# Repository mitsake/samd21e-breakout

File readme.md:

# Small SAMD21 breakout

This is a small, simple breakout for the Microchip (formerly Atmel) [ATSAMD21E][] series of chips in the TQFP package. I designed it mostly for something to do while locked down at home, but also so that I could use the bare ICs I had spare from previous projects.

[ATSAMD21E]: https://www.microchip.com/wwwproducts/en/ATSAMD21E18

Most I/O pins are broken out, with the exception of PA00/01 (XIN32 and XOUT32 for the watch crystal) and PA24/25 (D- and D+ for USB). The SWD interface is available via either the header, or through the [SOICbite][] connector opposite the USB footprint. There's an onboard regulator, crystal, reset button, and USB jack make things a bit more convenient. 

This design is based on Adafruit's [Trinket M0][] as well as Technoblogy's Minimal [ATSAMD21 Computer][minimalcomp].

[SOICbite]: https://github.com/SimonMerrett/SOICbite/
[Trinket M0]: https://www.adafruit.com/product/3500
[minimalcomp]: http://www.technoblogy.com/show?2833

## BoM

| Reference | Quantity | Value                      | Footprint                   |
| --------- | -------- | -------------------------- | --------------------------- |
| C1, C2    | 2        | 10 μF, > 6 V               | 0603                        |
| C3, C4    | 2        | 1 μF, > 4 V                | 0603                        |
| C5        | 1        | 0.1 μF, > 4 V              | 0603                        |
| C6, C7    | 2        | 10 pF, > 4 V               | 0603                        |
| J1        | 1        | Micro-USB jack             | [Molex 105017-0001][1]      |
| SW1       | 1        | Push switch                | [Alps SKRKAEE020][2]        |
| U1        | 1        | AP2112K-3.3                | SOT23-5                     |
| U2        | 1        | ATSAMD21Exx                | TQFP-32                     |
| Y1        | 1        | 32.768 kHz, < 12.5 pF load | [Micro Crystal CM7V-T1A][3] |

[1]: https://www.molex.com/molex/products/part-detail/io_connectors/1050170001
[2]: https://tech.alpsalpine.com/prod/e/html/tact/surfacemount/skrk/skrk_list.html
[3]: https://www.microcrystal.com/en/products/khz-quartz-crystals/cm7v-t1a/

## Schematic

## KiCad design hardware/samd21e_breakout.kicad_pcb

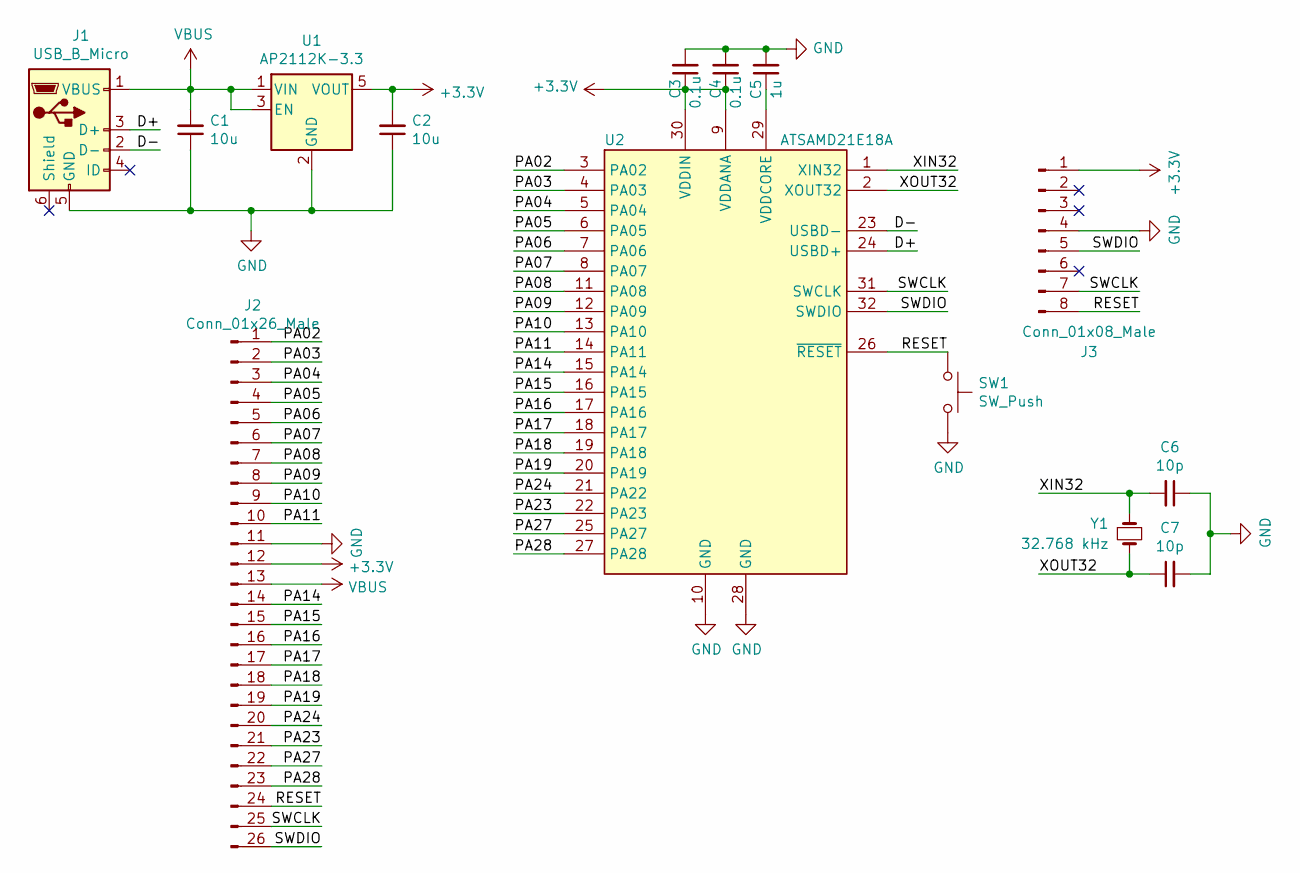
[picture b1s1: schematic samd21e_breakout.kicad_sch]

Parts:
C1, C2: 10u; C_0603_NoSilk
C3, C4: 0.1u; C_0603_NoSilk
C5: 1u; C_0603_NoSilk
C6, C7: 10p; C_0603_NoSilk
J1: USB_B_Micro; Molex-105017-0001
J2: Conn_01x26_Male; PinHeader_2x13_Breadboard_Spaced
J3: Conn_01x08_Male; SOIC_clipProgSmall
SW1: SW_Push; SW_Push_Alps_SKRK_NoSilk
U1: AP2112K-3.3; SOT-23-5_NoSilk
U2: ATSAMD21E18A; TQFP-32_NoSilk
Y1: 32.768 kHz; CM7V-T1A

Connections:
+3V3: C2.2, C3.1, C4.1, J2.12, J3.1, U1.5 (VOUT), U2.9 (VDDANA), U2.30 (VDDIN)
/D+: J1.3 (D+), U2.24 (USBD+)
/D-: J1.2 (D-), U2.23 (USBD-)
/PA02: J2.1, U2.3 (PA02)
/PA03: J2.2, U2.4 (PA03)
/PA04: J2.3, U2.5 (PA04)
/PA05: J2.4, U2.6 (PA05)
/PA06: J2.5, U2.7 (PA06)
/PA07: J2.6, U2.8 (PA07)
/PA08: J2.7, U2.11 (PA08)
/PA09: J2.8, U2.12 (PA09)
/PA10: J2.9, U2.13 (PA10)
/PA11: J2.10, U2.14 (PA11)
/PA14: J2.14, U2.15 (PA14)
/PA15: J2.15, U2.16 (PA15)
/PA16: J2.16, U2.17 (PA16)
/PA17: J2.17, U2.18 (PA17)
/PA18: J2.18, U2.19 (PA18)
/PA19: J2.19, U2.20 (PA19)
/PA23: J2.21, U2.22 (PA23)
/PA24: J2.20, U2.21 (PA22)
/PA27: J2.22, U2.25 (PA27)
/PA28: J2.23, U2.27 (PA28)
/RESET: J2.24, J3.8, SW1.1, U2.26 (~RESET)
/SWCLK: J2.25, J3.7, U2.31 (SWCLK)
/SWDIO: J2.26, J3.5, U2.32 (SWDIO)
/XIN32: C6.2, U2.1 (XIN32), Y1.1
/XOUT32: C7.1, U2.2 (XOUT32), Y1.2
GND: C1.1, C2.1, C3.2, C4.2, C5.2, C6.1, C7.2, J1.5 (GND), J2.11, J3.4, SW1.2, U1.2 (GND), U2.10 (GND), U2.28 (GND)
unnamed: C5.1, U2.29 (VDDCORE)
VBUS: C1.2, J1.1 (VBUS), J2.13, U1.1 (VIN), U1.3 (EN)

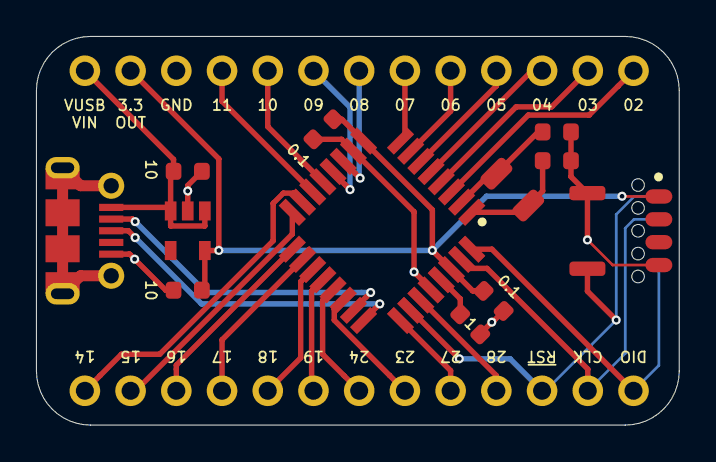
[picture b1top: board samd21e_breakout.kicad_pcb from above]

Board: 2 copper layers, 35.7 x 21.6 mm, 14 parts (0 on the bottom side), 31 nets.

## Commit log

2020-04-19 Added link to SOICbite project
2020-05-01 added some images at a licence
2020-06-12 added load capacitors to schematic and pcb
2020-06-12 updated schematic image
2022-02-10 Long overdue update to readme, upgrade to KiCad 6
2022-02-10 Further readme update
